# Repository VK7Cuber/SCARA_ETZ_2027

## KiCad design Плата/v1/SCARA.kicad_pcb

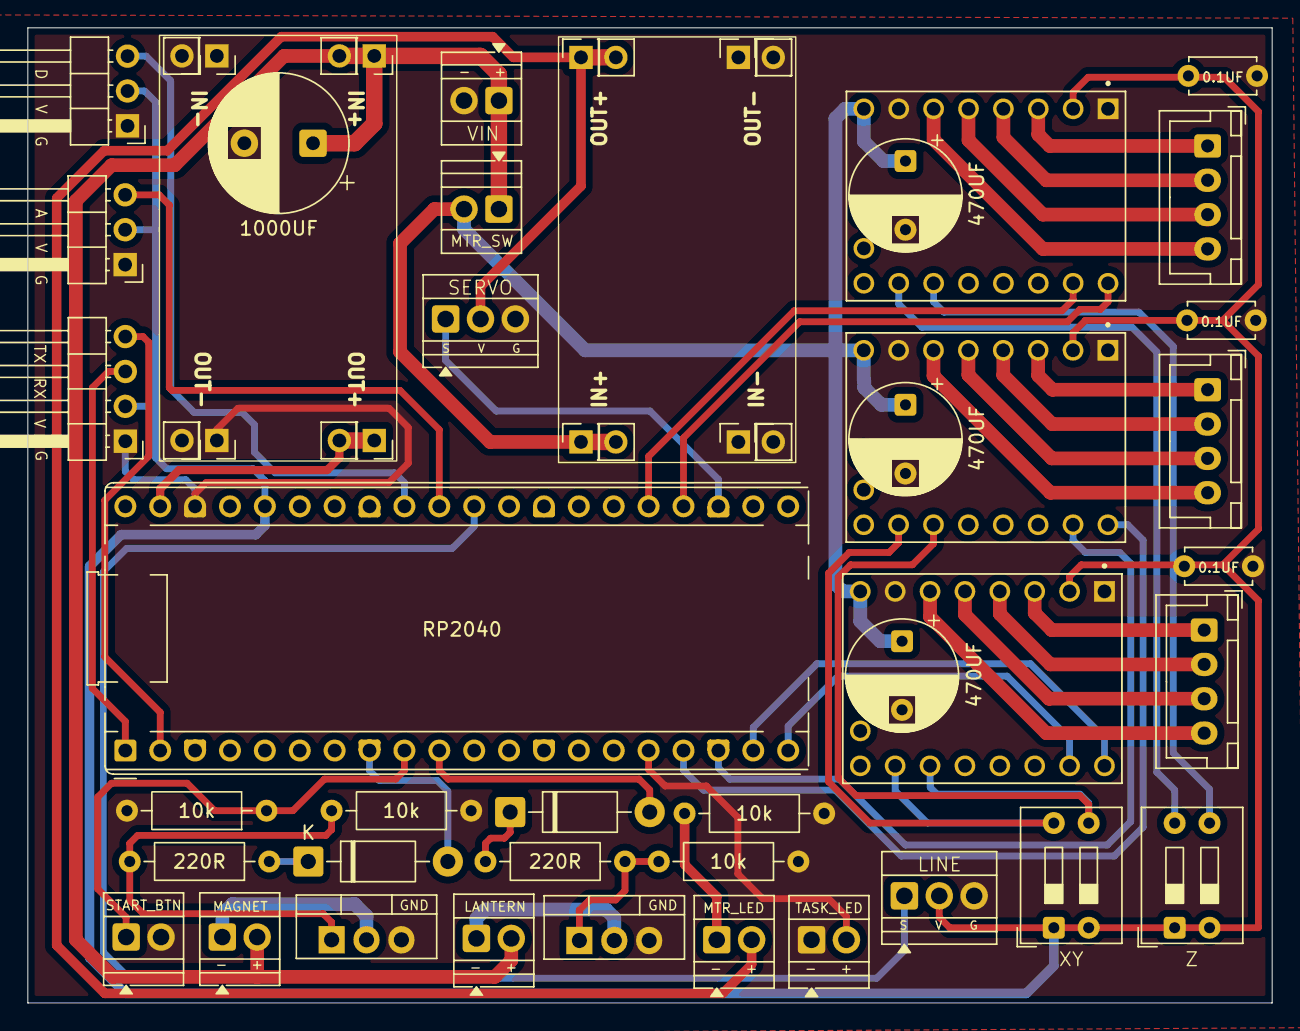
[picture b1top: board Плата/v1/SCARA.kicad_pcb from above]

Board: 2 copper layers, 90.6 x 71.0 mm, 40 parts (0 on the bottom side), 45 nets.

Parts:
0.1мк2, 0.2, 0.3: CK1; C_Disc_D4.7mm_W2.5mm_P5.00mm
10k, 10k#2: R; R_Axial_DIN0207_L6.3mm_D2.5mm_P10.16mm_Horizontal
10k#3, 10k#4: 10k; R_Axial_DIN0207_L6.3mm_D2.5mm_P10.16mm_Horizontal
220R, 220R#2: 220R; R_Axial_DIN0207_L6.3mm_D2.5mm_P10.16mm_Horizontal
470UF: 470мк; CP_Radial_D8.0mm_P5.00mm
1000UF: 1000мк; CP_Radial_D10.0mm_P5.00mm
C2, C3: 470мк; CP_Radial_D8.0mm_P5.00mm
D2, D3: 1N4007; D_DO-41_SOD81_P10.16mm_Horizontal
J1, J3, J13: Conn_01x02_Socket; TerminalBlock_Xinya_XY308-2.54-2P_1x02_P2.54mm_Horizontal
J2, J10, J14, J15: Lantern_1; TerminalBlock_Xinya_XY308-2.54-2P_1x02_P2.54mm_Horizontal
J4, J5, J6: Conn_01x04_Male; JST_XH_B4B-XH-A_1x04_P2.50mm_Vertical
J7, J8: Conn_01x03_Socket; TerminalBlock_Xinya_XY308-2.54-3P_1x03_P2.54mm_Horizontal
J9, J11: Conn_01x03_Pin; PinHeader_1x03_P2.54mm_Horizontal
J12: Conn_01x04_Pin; PinHeader_1x04_P2.54mm_Horizontal
Q1, Q2: Transistor; TO-220-3_Vertical
RP2040: RaspberryPi_Pico_Common_THT
SW1, SW2: SW_DIP_x02; SW_DIP_SPSTx02_Slide_9.78x7.26mm_W7.62mm_P2.54mm
TMC_L1: MODULE_TMC2209_SILENTSTEPSTICK
TMC_R1: MODULE_TMC2209_SILENTSTEPSTICK
TMC_Z1: MODULE_TMC2209_SILENTSTEPSTICK
U1, U2: Mini650pro; Mini560pro

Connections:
3.3V: 0.1мк2.1, 0.2.1, 0.3.1, J8.2, J9.2, J11.2, J12.2, RP2040.36 (3V3), SW1.1, SW1.2, SW2.1, SW2.2, TMC_L1.2 (VIO), TMC_R1.2 (VIO), TMC_Z1.2 (VIO)
5V_MOTORS: J7.2, J15.2, U2.4 (OUT+)
ANALOG_PIN: J11.3, RP2040.31 (GP27_A1)
DIGITAL_PIN: J9.3, RP2040.32 (GP28_A2)
DIR_L: RP2040.19 (GP16), TMC_L1.9 (DIR)
DIR_R: RP2040.17 (GP14), TMC_R1.9 (DIR)
DIR_Z: RP2040.24 (GP21), TMC_Z1.9 (DIR)
GND: 0.1мк2.2, 0.2.2, 0.3.2, 10k.2, 10k#2.1, 10k#3.1, 10k#4.1, 470UF.2, 1000UF.2, C2.2, C3.2, J1.2, J7.3, J8.3, J9.1, J11.1, J12.1, J13.2, J14.1, Q1.3 (S), Q2.3 (S), RP2040.38 (GND), TMC_L1.1 (GND), TMC_L1.7 (GND), TMC_R1.1 (GND), TMC_R1.7 (GND), TMC_Z1.1 (GND), TMC_Z1.7 (GND), U1.2 (IN-), U1.3 (OUT-), U2.2 (IN-), U2.3 (OUT-)
LANTERN_PIN: D2.2 (A), RP2040.10 (GP8)
LINE_SENSOR_PIN: J8.1, RP2040.30 (GP26_A0)
MAGNET_PIN: D3.2 (A), RP2040.8 (GP6)
MOTORS: 470UF.1, C2.1, C3.1, J3.2, TMC_L1.8 (VM), TMC_R1.8 (VM), TMC_Z1.8 (VM), U2.1 (IN+)
MS1_XY: SW1.4, TMC_L1.15 (MS1), TMC_R1.15 (MS1)
MS1_Z: SW2.4, TMC_Z1.15 (MS1)
MS2_XY: SW1.3, TMC_L1.14 (MS2), TMC_R1.14 (MS2)
MS2_Z: SW2.3, TMC_Z1.14 (MS2)
unnamed: 220R.1, D2.1 (K)
unnamed: 220R#2.1, D3.1 (K)
unnamed: J2.1, Q2.2 (D)
unnamed: J4.1, TMC_R1.3 (B2)
unnamed: J4.2, TMC_R1.4 (BT)
unnamed: J4.3, TMC_R1.5 (A1)
unnamed: J4.4, TMC_R1.6 (A2)
unnamed: J5.1, TMC_L1.3 (B2)
unnamed: J5.2, TMC_L1.4 (BT)
unnamed: J5.3, TMC_L1.5 (A1)
unnamed: J5.4, TMC_L1.6 (A2)
unnamed: J6.1, TMC_Z1.3 (B2)
unnamed: J6.2, TMC_Z1.4 (BT)
unnamed: J6.3, TMC_Z1.5 (A1)
unnamed: J6.4, TMC_Z1.6 (A2)
unnamed: J10.1, Q1.2 (D)
unnamed: 10k#2.2, J15.1
unnamed: 10k#3.2, 220R.2, Q1.1 (G)
unnamed: 10k#4.2, 220R#2.2, Q2.1 (G)
RX: J12.3, RP2040.1 (GP0)
SERVO_PIN: J7.1, RP2040.23 (GP20)
START_BUTTON_PIN: 10k.1, J13.1, RP2040.9 (GP7)
STEP_L: RP2040.20 (GP17), TMC_L1.10 (STEP)
STEP_R: RP2040.18 (GP15), TMC_R1.10 (STEP)
STEP_Z: RP2040.25 (GP22), TMC_Z1.10 (STEP)
TASK_LED: J14.2, RP2040.16 (GP13)
TX: J12.4, RP2040.2 (GP1)
VCC: RP2040.39 (VIN), U1.4 (OUT+)
VIN: 1000UF.1, J1.1, J2.2, J3.1, J10.2, U1.1 (IN+)

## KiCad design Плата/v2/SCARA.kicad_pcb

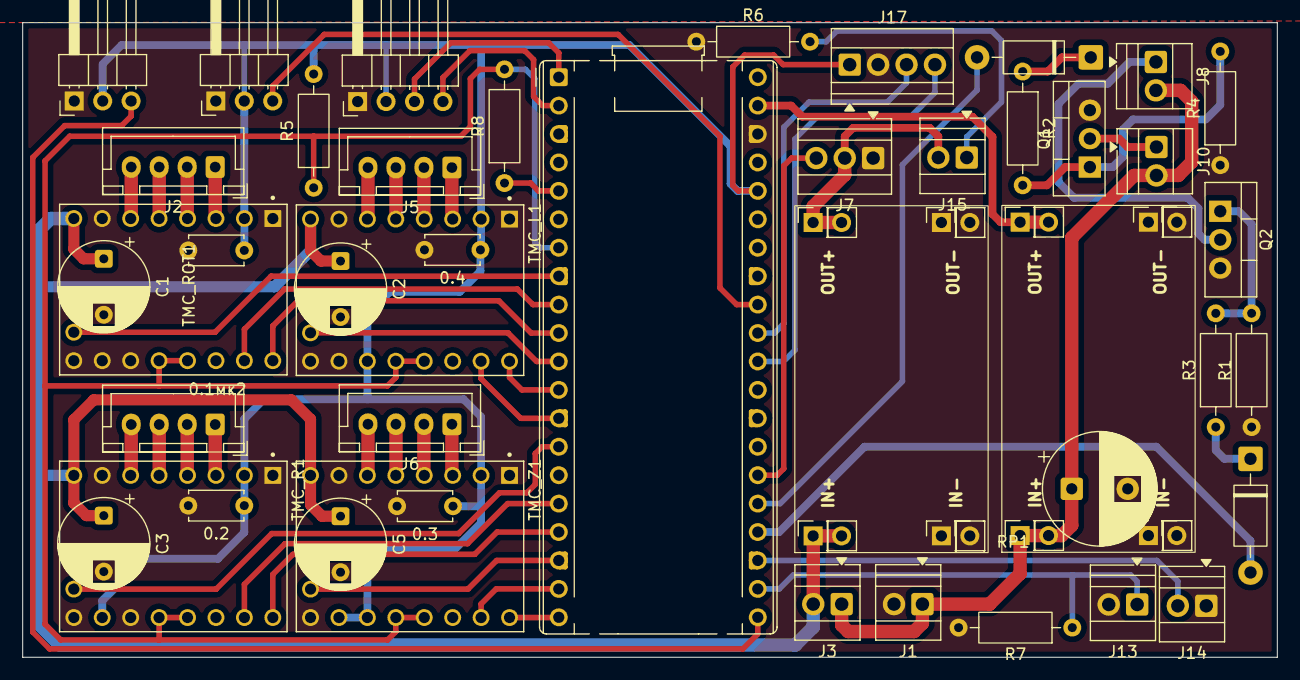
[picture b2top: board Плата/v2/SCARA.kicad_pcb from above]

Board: 2 copper layers, 112.1 x 56.7 mm, 44 parts (0 on the bottom side), 54 nets.

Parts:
0.1мк2, 0.2, 0.3, 0.4: CK1; C_Disc_D4.7mm_W2.5mm_P5.00mm
C1, C2, C3, C5: 470мк; CP_Radial_D8.0mm_P5.00mm
C4: 1000мк; CP_Radial_D10.0mm_P5.00mm
D2, D3: 1N4007; D_DO-41_SOD81_P10.16mm_Horizontal
J1, J3, J13: Conn_01x02_Socket; TerminalBlock_Xinya_XY308-2.54-2P_1x02_P2.54mm_Horizontal
J2, J4, J5, J6: Conn_01x04_Male; JST_XH_B4B-XH-A_1x04_P2.50mm_Vertical
J7: Conn_01x03_Pin; TerminalBlock_Xinya_XY308-2.54-3P_1x03_P2.54mm_Horizontal
J8, J10, J14, J15: Lantern_1; TerminalBlock_Xinya_XY308-2.54-2P_1x02_P2.54mm_Horizontal
J9, J11: Conn_01x03_Pin; PinHeader_1x03_P2.54mm_Horizontal
J12: Conn_01x04_Pin; PinHeader_1x04_P2.54mm_Horizontal
J17: Conn_01x04_Pin; TerminalBlock_Xinya_XY308-2.54-4P_1x04_P2.54mm_Horizontal
Q1, Q2: Transistor; TO-220-3_Vertical
R1, R4: 10k; R_Axial_DIN0207_L6.3mm_D2.5mm_P10.16mm_Horizontal
R2, R3: 220R; R_Axial_DIN0207_L6.3mm_D2.5mm_P10.16mm_Horizontal
R5, R8: 1k; R_Axial_DIN0207_L6.3mm_D2.5mm_P10.16mm_Horizontal
R6, R7: R; R_Axial_DIN0207_L6.3mm_D2.5mm_P10.16mm_Horizontal
RP1: RaspberryPi_Pico_Common_THT
TMC_L1: MODULE_TMC2209_SILENTSTEPSTICK
TMC_R1: MODULE_TMC2209_SILENTSTEPSTICK
TMC_ROT1: MODULE_TMC2209_SILENTSTEPSTICK
TMC_Z1: MODULE_TMC2209_SILENTSTEPSTICK
U1, U2: Mini650pro; Mini560pro

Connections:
3.3V: 0.1мк2.1, 0.2.1, 0.3.1, 0.4.1, J9.2, J11.2, J12.2, J17.1, R5.2, RP1.36 (3V3), TMC_L1.2 (VIO), TMC_L1.14 (MS2), TMC_R1.2 (VIO), TMC_R1.15 (MS1), TMC_ROT1.2 (VIO), TMC_Z1.2 (VIO), TMC_Z1.14 (MS2), TMC_Z1.15 (MS1)
5V_MOTORS: J7.2, J15.2, U2.4 (OUT+)
ANALOG_PIN: J11.3, RP1.32 (GP28_A2)
DIAG_L: RP1.11 (GP9), TMC_L1.18 (DIAG)
DIAG_R: RP1.14 (GP12), TMC_R1.18 (DIAG)
DIAG_ROT: RP1.8 (GP6), TMC_ROT1.18 (DIAG)
DIAG_Z: RP1.18 (GP15), TMC_Z1.18 (DIAG)
DIGITAL_PIN: J9.3, RP1.21 (GP18)
DIR_L: RP1.12 (GP10), TMC_L1.9 (DIR)
DIR_R: RP1.17 (GP14), TMC_R1.9 (DIR)
DIR_ROT: RP1.10 (GP8), TMC_ROT1.9 (DIR)
DIR_Z: RP1.20 (GP17), TMC_Z1.9 (DIR)
DIST_SENSOR_SCL: J17.3, RP1.31 (GP27_A1)
DIST_SENSOR_SDA: J17.4, RP1.30 (GP26_A0)
DRIVERS_UART: R5.1, R8.2, RP1.7 (GP5), TMC_L1.12 (RX), TMC_L1.13 (TX), TMC_R1.12 (RX), TMC_R1.13 (TX), TMC_ROT1.12 (RX), TMC_ROT1.13 (TX), TMC_Z1.12 (RX), TMC_Z1.13 (TX)
GND: 0.1мк2.2, 0.2.2, 0.3.2, 0.4.2, C1.2, C2.2, C3.2, C4.2, C5.2, J1.2, J7.1, J9.1, J11.1, J12.1, J13.2, J14.1, J17.2, Q1.3 (S), Q2.3 (S), R1.1, R4.1, R6.1, R7.2, RP1.38 (GND), TMC_L1.1 (GND), TMC_L1.7 (GND), TMC_L1.15 (MS1), TMC_L1.16 (EN), TMC_R1.1 (GND), TMC_R1.7 (GND), TMC_R1.14 (MS2), TMC_R1.16 (EN), TMC_ROT1.1 (GND), TMC_ROT1.7 (GND), TMC_ROT1.14 (MS2), TMC_ROT1.15 (MS1), TMC_ROT1.16 (EN), TMC_Z1.1 (GND), TMC_Z1.7 (GND), TMC_Z1.16 (EN), U1.2 (IN-), U1.3 (OUT-), U2.2 (IN-), U2.3 (OUT-)
MOTORS: C1.1, C2.1, C3.1, C5.1, J3.2, TMC_L1.8 (VM), TMC_R1.8 (VM), TMC_ROT1.8 (VM), TMC_Z1.8 (VM), U2.1 (IN+)
unnamed: D2.1 (K), R2.1
unnamed: D3.1 (K), R3.1
unnamed: J2.1, TMC_ROT1.3 (B2)
unnamed: J2.2, TMC_ROT1.4 (BT)
unnamed: J2.3, TMC_ROT1.5 (A1)
unnamed: J2.4, TMC_ROT1.6 (A2)
unnamed: J4.1, TMC_R1.3 (B2)
unnamed: J4.2, TMC_R1.4 (BT)
unnamed: J4.3, TMC_R1.5 (A1)
unnamed: J4.4, TMC_R1.6 (A2)
unnamed: J5.1, TMC_L1.3 (B2)
unnamed: J5.2, TMC_L1.4 (BT)
unnamed: J5.3, TMC_L1.5 (A1)
unnamed: J5.4, TMC_L1.6 (A2)
unnamed: J6.1, TMC_Z1.3 (B2)
unnamed: J6.2, TMC_Z1.4 (BT)
unnamed: J6.3, TMC_Z1.5 (A1)
unnamed: J6.4, TMC_Z1.6 (A2)
unnamed: J8.1, Q2.2 (D)
unnamed: J10.1, Q1.2 (D)
unnamed: J15.1, R6.2
unnamed: Q1.1 (G), R2.2, R4.2
unnamed: Q2.1 (G), R1.2, R3.2
unnamed: R8.1, RP1.5 (GP4)
PUMP_PIN: D2.2 (A), RP1.25 (GP22)
RX: J12.3, RP1.1 (GP0)
SERVO_PIN: J7.3, RP1.26 (GP23)
START_BUTTON_PIN: J13.1, R7.1, RP1.22 (GP19)
STEP_L: RP1.13 (GP11), TMC_L1.10 (STEP)
STEP_R: RP1.16 (GP13), TMC_R1.10 (STEP)
STEP_ROT: RP1.9 (GP7), TMC_ROT1.10 (STEP)
STEP_Z: RP1.19 (GP16), TMC_Z1.10 (STEP)
TASK_LED: J14.2, RP1.23 (GP20)
TX: J12.4, RP1.2 (GP1)
VALVE_PIN: D3.2 (A), RP1.24 (GP21)
VCC: RP1.39 (VIN), U1.4 (OUT+)
VIN: C4.1, J1.1, J3.1, J8.2, J10.2, U1.1 (IN+)
